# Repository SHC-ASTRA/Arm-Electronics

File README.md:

View this project on [CADLAB.io](https://cadlab.io/project/23351). 

# Arm-Electronics

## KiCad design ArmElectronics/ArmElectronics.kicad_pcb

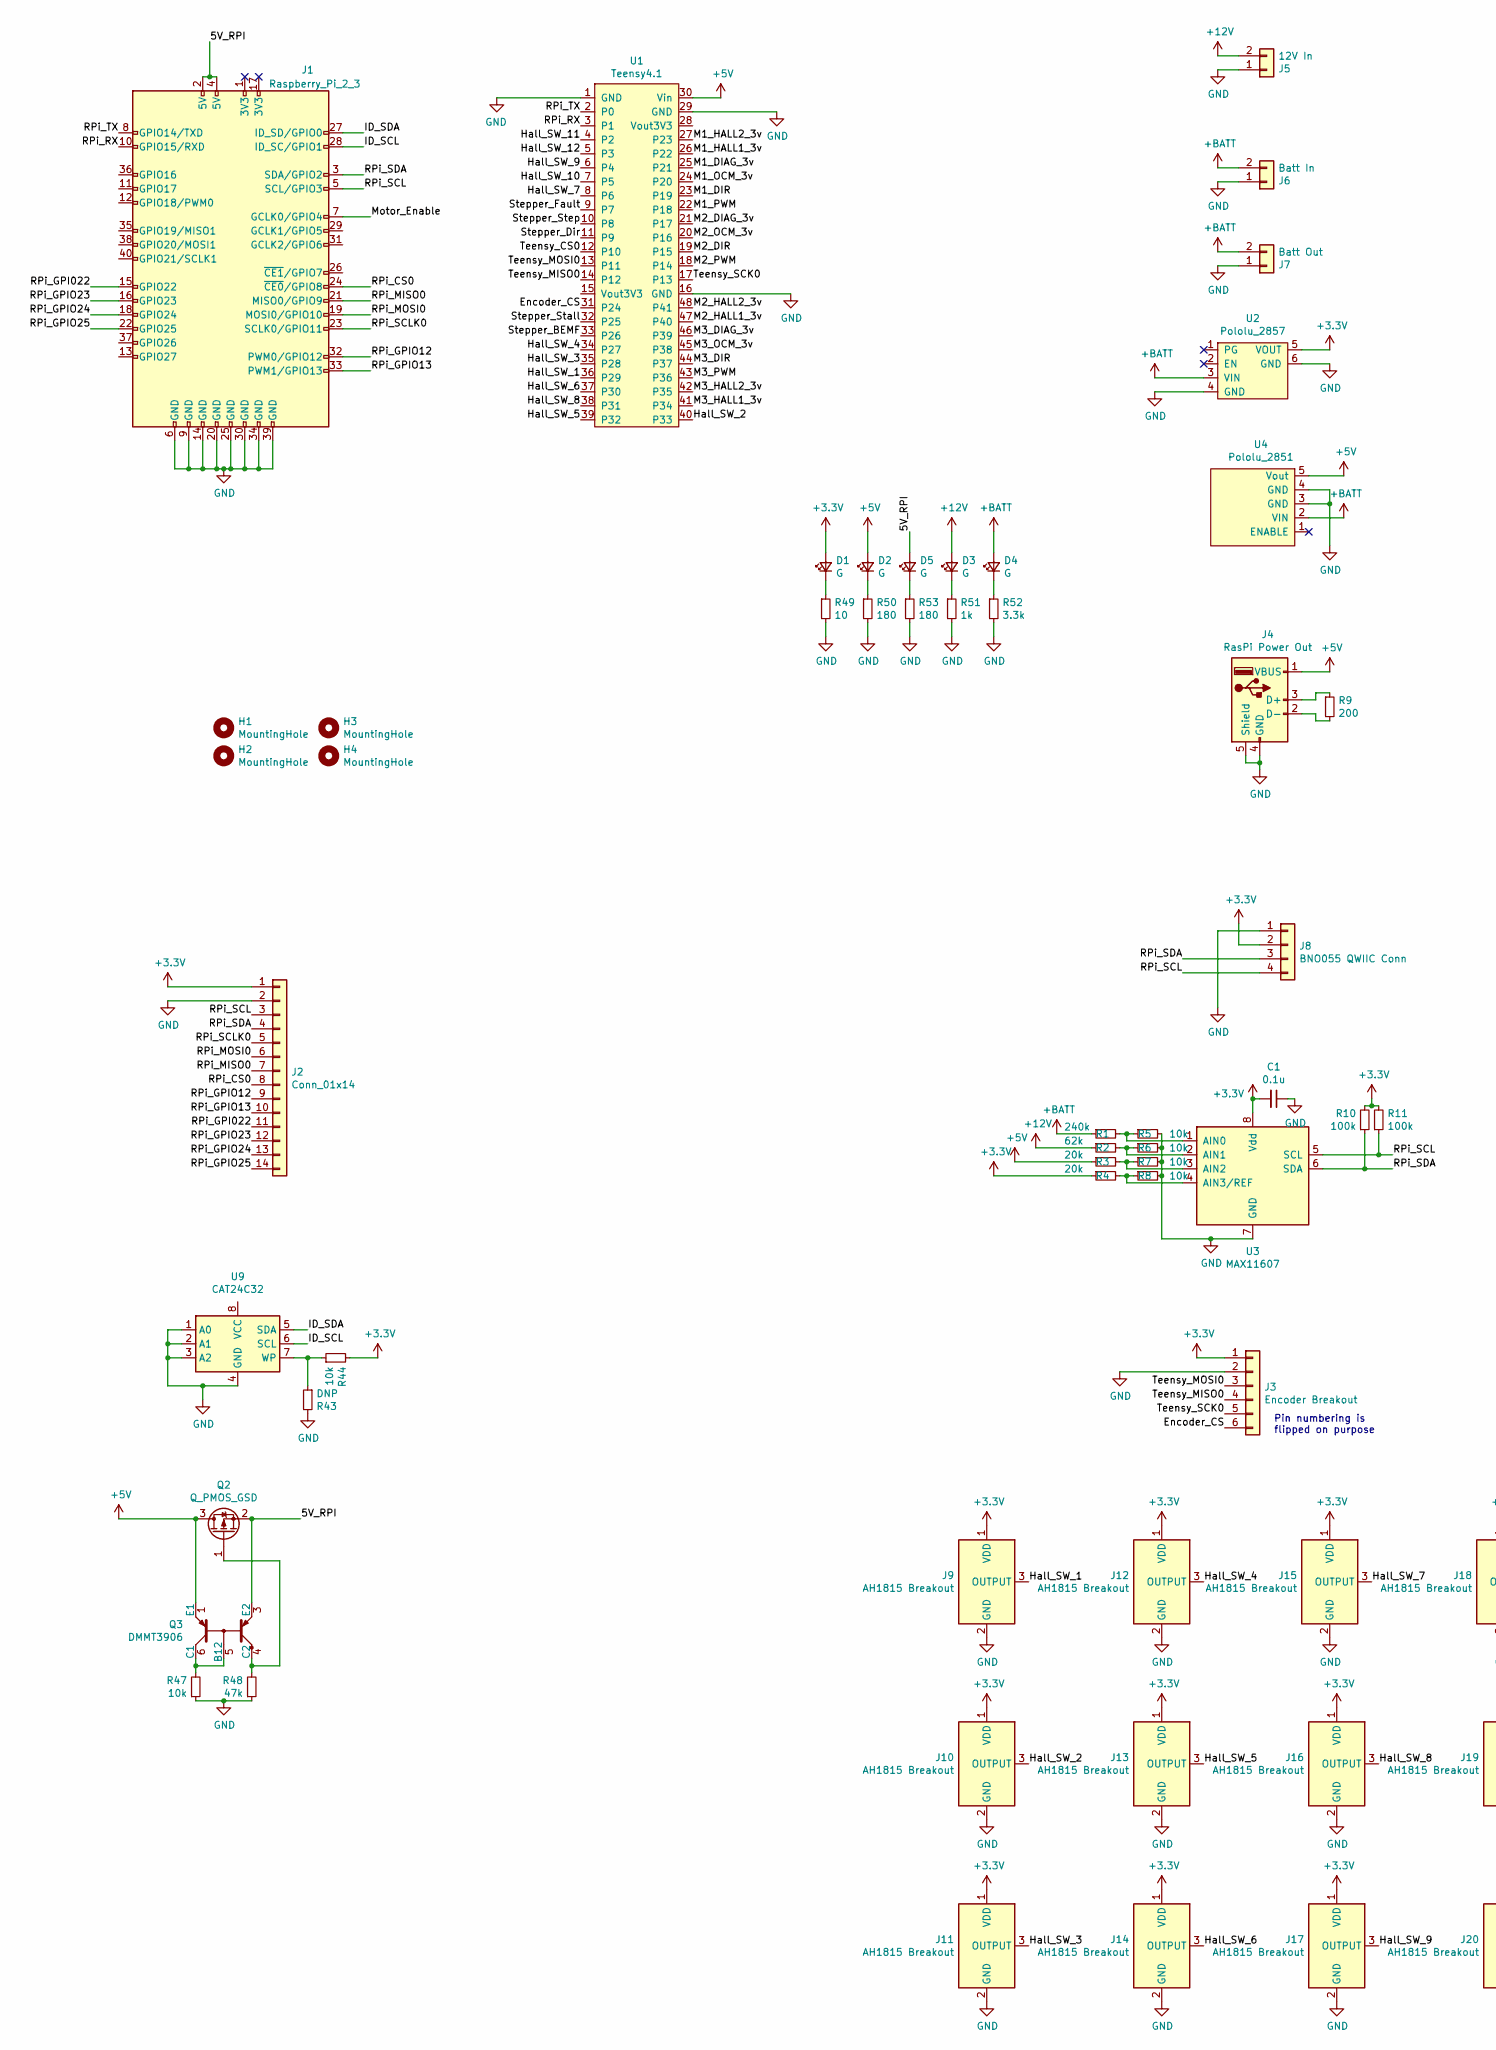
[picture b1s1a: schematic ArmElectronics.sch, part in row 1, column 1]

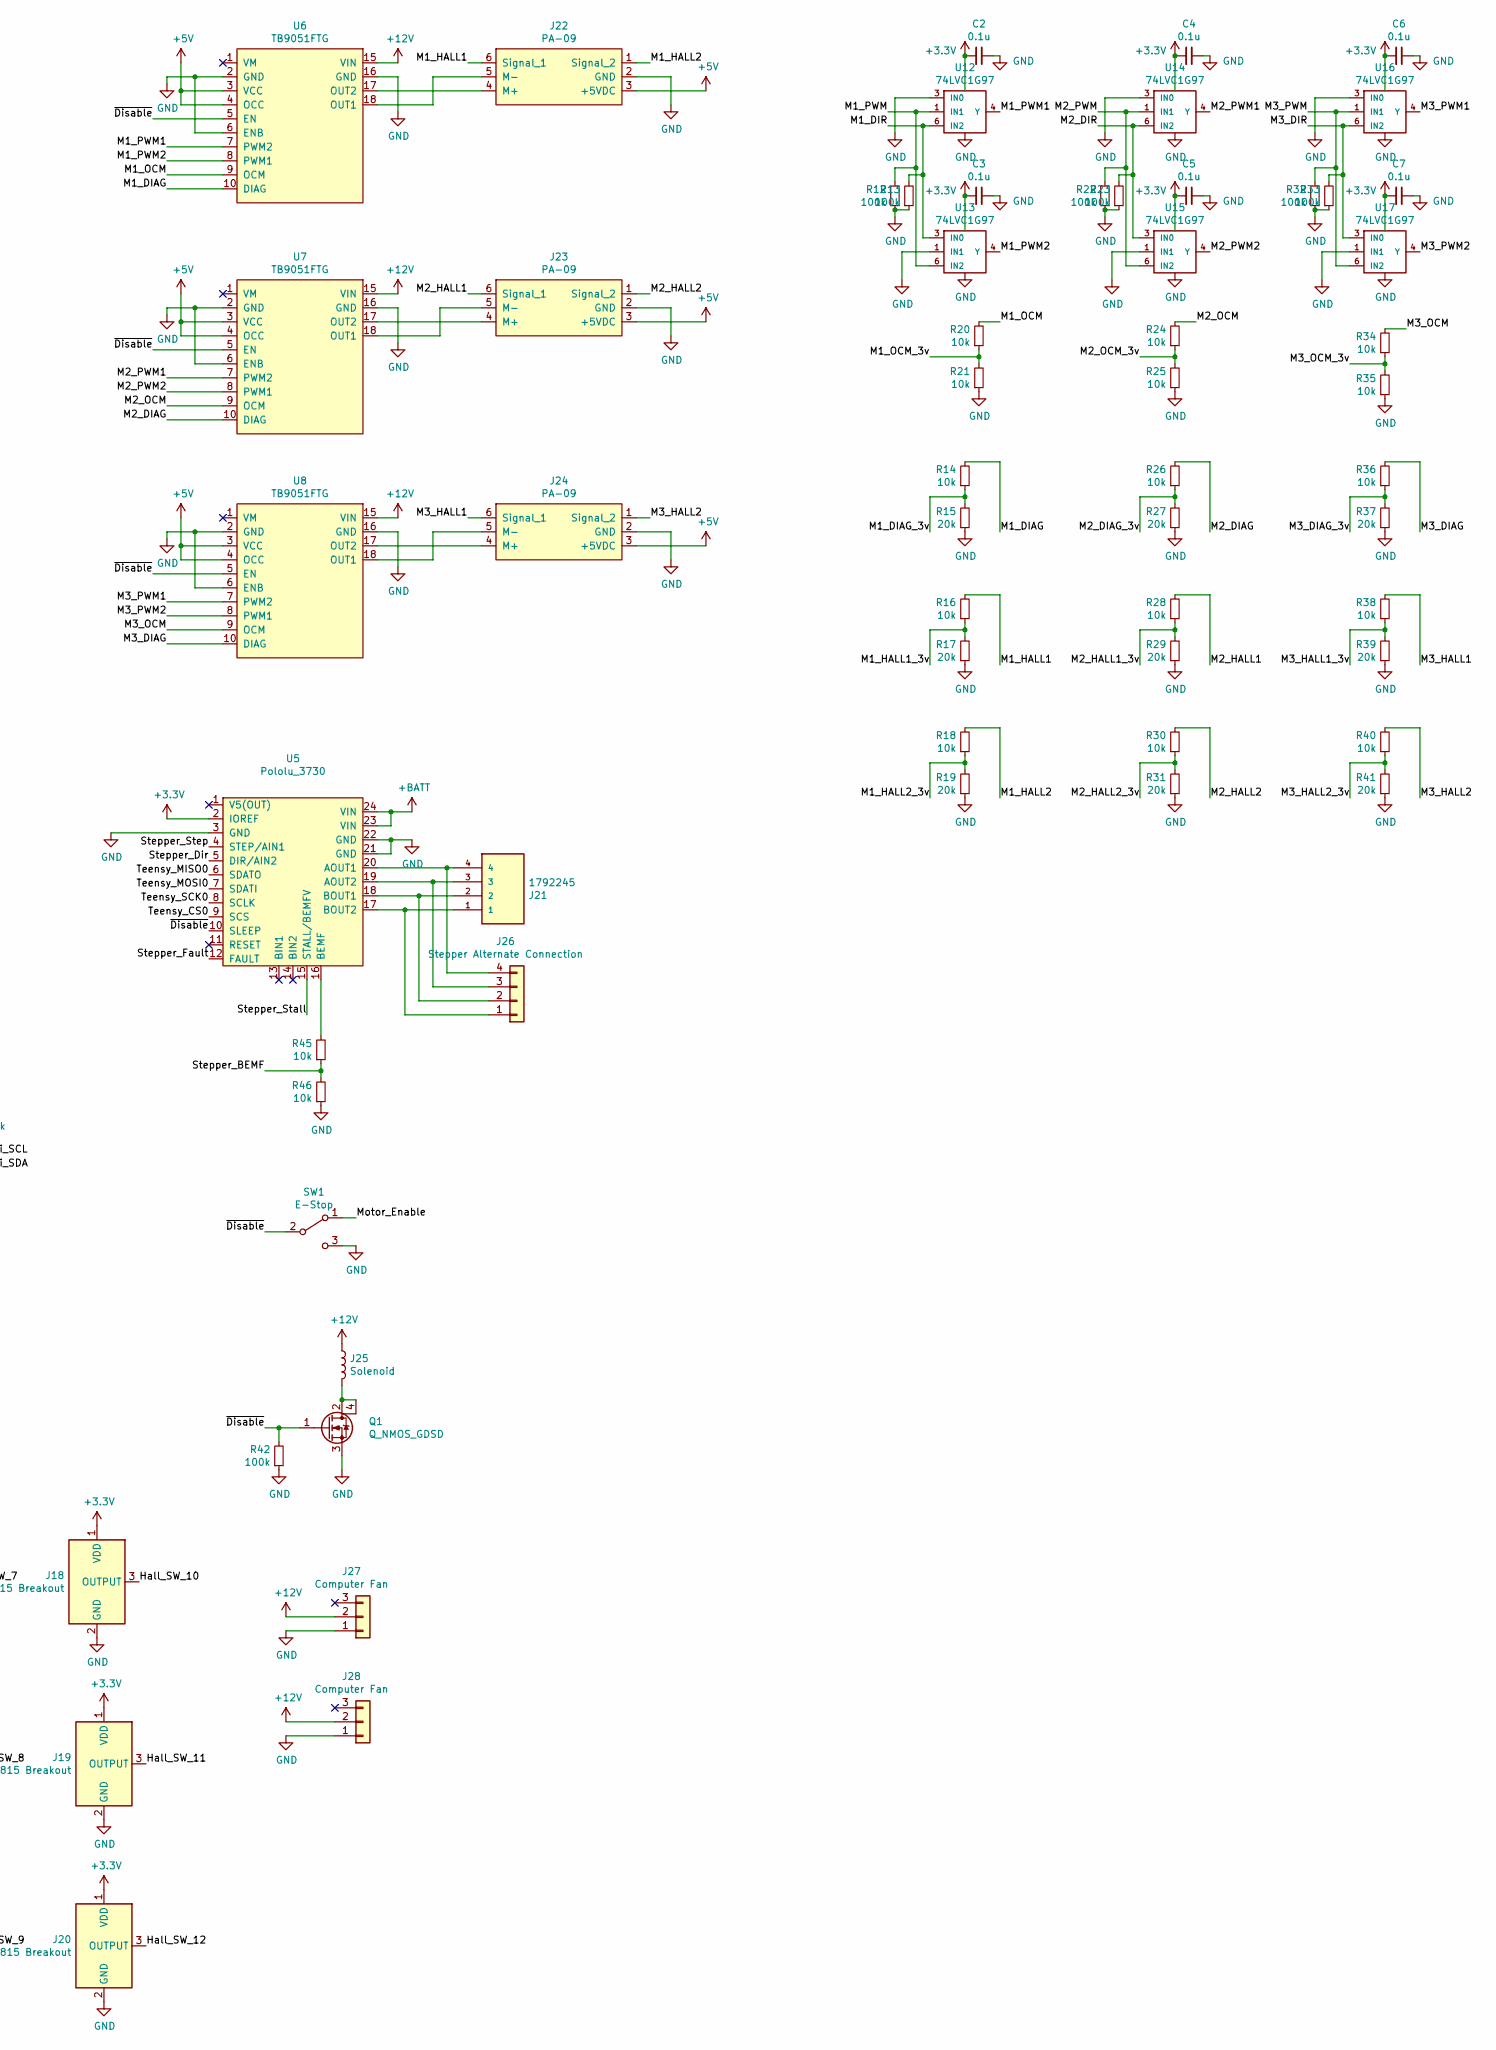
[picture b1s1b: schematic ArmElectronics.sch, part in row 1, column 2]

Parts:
C1, C2, C3, C4, C5, C6, C7: 0.1u; C_0603_1608Metric_Pad1.05x0.95mm_HandSolder; Digikey Part Num 311-1341-1-ND
D1, D2, D3, D4, D5: G; LED_0603_1608Metric_Pad1.05x0.95mm_HandSolder; Digikey Part Num 732-4971-1-ND
H1, H2, H3, H4: MountingHole; MountingHole_3.2mm_M3_Pad
J1: Raspberry_Pi_2_3; IDC-Header_2x20_P2.54mm_Vertical; Digikey Part Num S9175-ND
J2: Conn_01x14; PinSocket_1x14_P2.54mm_Vertical
J3: Encoder Breakout; JST_PH_B6B-PH-K_1x06_P2.00mm_Vertical; Digikey Part Num 455-1708-ND
J4: RasPi Power Out; USB_A_Molex_67643_Horizontal; Digikey Part Num WM14667-ND
J5: 12V In; AMASS_XT60-F_1x02_P7.20mm_Vertical; Digikey Part Num not on Digikey
J6: Batt In; AMASS_XT60-F_1x02_P7.20mm_Vertical; Digikey Part Num not on Digikey
J7: Batt Out; AMASS_XT60-F_1x02_P7.20mm_Vertical; Digikey Part Num not on Digikey
J8: BNO055 QWIIC Conn; JST_SH_SM04B-SRSS-TB_1x04-1MP_P1.00mm_Horizontal; Digikey Part Num 1528-4646-ND
J9, J10, J11, J12, J13, J14, J15, J16, J17, J18, J19, J20: AH1815 Breakout; JST_PH_B3B-PH-K_1x03_P2.00mm_Vertical; Digikey Part Num 455-1705-ND
J21: 1792245; PHOENIX_1792245; PARTREV 29.08.2013; Digikey Part Num 277-9888-ND
J22, J23, J24: PA-09; Molex_Mini-Fit_Jr_5566-06A_2x03_P4.20mm_Vertical; Digikey Part Num WM3802-ND
J25: Solenoid; JST_XH_B2B-XH-A_1x02_P2.50mm_Vertical; Digikey Part Num 455-2247-ND
J26: Stepper Alternate Connection; JST_XH_S4B-XH-A_1x04_P2.50mm_Horizontal; Digikey Part Num 455-2243-ND
J27, J28: Computer Fan; Molex_KK-254_AE-6410-03A_1x03_P2.54mm_Vertical; Digikey Part Num WM2701-ND
Q1: Q_NMOS_GDSD; SOT-223; Digikey Part Num NCV8440ASTT1GOSCT-ND
Q2: Q_PMOS_GSD; SOT-23; Digikey Part Num TSM500P02CXRFGCT-ND
Q3: DMMT3906; SOT-23-6; Digikey Part Num DMMT3906-7-FDICT-ND
R1: 240k; R_0603_1608Metric_Pad0.98x0.95mm_HandSolder; Digikey Part Num P240KGCT-ND
R2: 62k; R_0603_1608Metric_Pad0.98x0.95mm_HandSolder; Digikey Part Num P62KGCT-ND
R3, R4, R15, R17, R19, R27, R29, R31, R37, R39, R41: 20k; R_0603_1608Metric_Pad0.98x0.95mm_HandSolder; Digikey Part Num P20KGCT-ND
R5, R6, R7, R8, R14, R16, R18, R20, R21, R24, R25, R26, R28, R30, R34, R35, R36, R38, R40, R44, R45, R46, R47: 10k; R_0603_1608Metric_Pad0.98x0.95mm_HandSolder; Digikey Part Num P10KGCT-ND
R9: 200; R_0603_1608Metric_Pad0.98x0.95mm_HandSolder; Digikey Part Num P200GCT-ND
R10, R11, R12, R13, R22, R23, R32, R33, R42: 100k; R_0603_1608Metric_Pad0.98x0.95mm_HandSolder; Digikey Part Num P100KGCT-ND
R43: DNP; R_0603_1608Metric_Pad0.98x0.95mm_HandSolder
R48: 47k; R_0603_1608Metric_Pad0.98x0.95mm_HandSolder; Digikey Part Num 311-47.0KHRCT-ND
R49: 10; R_0603_1608Metric; Digikey Part Num 311-10.0HRCT-ND
R50, R53: 180; R_0603_1608Metric; Digikey Part Num 311-180HRCT-ND
R51: 1k; R_0603_1608Metric; Digikey Part Num 311-1.00KHRCT-ND
R52: 3.3k; R_0603_1608Metric; Digikey Part Num 311-3.30KHRCT-ND
SW1: E-Stop; JST_PH_B3B-PH-K_1x03_P2.00mm_Vertical; Digikey Part Num 455-1705-ND
U1: Teensy4.1; Digikey Part Num 1568-DEV-16996-ND
U2: Pololu_2857; Digikey Part Num 2183-2857-ND
U3: MAX11607; TSSOP-8_3x3mm_P0.65mm; Digikey Part Num MAX11607EUA+-ND
U4: Pololu_2851; Digikey Part Num 2183-2851-ND
U5: Pololu_3730; Digikey Part Num 2183-3730-ND
U6, U7, U8: TB9051FTG; Digikey Part Num 2183-2997-ND
U9: CAT24C32; TSSOP-8_4.4x3mm_P0.65mm; Digikey Part Num CAT24C32YI-GT3OSCT-ND
U12, U13, U14, U15, U16, U17: 74LVC1G97; SOT-23-6_Handsoldering; Digikey Part Num 296-15581-1-ND

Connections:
+3V3: C1.2, C2.2, C3.2, C4.2, C5.2, C6.2, C7.2, D1.2 (A), J2.1, J3.1, J8.2, J9.1 (VDD), J10.1 (VDD), J11.1 (VDD), J12.1 (VDD), J13.1 (VDD), J14.1 (VDD), J15.1 (VDD), J16.1 (VDD), J17.1 (VDD), J18.1 (VDD), J19.1 (VDD), J20.1 (VDD), R4.1, R10.2, R11.2, R44.2, U2.5 (VOUT), U3.8 (Vdd), U5.2 (IOREF), U12.5 (VCC), U13.5 (VCC), U14.5 (VCC), U15.5 (VCC), U16.5 (VCC), U17.5 (VCC)
+5V: D2.2 (A), J4.1 (VBUS), J22.3 (+5VDC), J23.3 (+5VDC), J24.3 (+5VDC), Q2.3 (D), Q3.1 (E1), R3.1, U1.30 (Vin), U4.5 (Vout), U6.3 (VCC), U6.4 (OCC), U7.3 (VCC), U7.4 (OCC), U8.3 (VCC), U8.4 (OCC)
+12V: D3.2 (A), J5.2, J25.1, J27.2, J28.2, R2.1, U6.15 (VIN), U7.15 (VIN), U8.15 (VIN)
+BATT: D4.2 (A), J6.2, J7.2, R1.1, U2.3 (VIN), U4.2 (VIN), U5.23 (VIN), U5.24 (VIN)
/5V_RPI: D5.2 (A), J1.2 (5V), J1.4 (5V), Q2.2 (S), Q3.3 (E2)
/Encoder_CS: J3.6, U1.31 (P24)
/Hall_SW_1: J9.3 (OUTPUT), U1.36 (P29)
/Hall_SW_2: J10.3 (OUTPUT), U1.40 (P33)
/Hall_SW_3: J11.3 (OUTPUT), U1.35 (P28)
/Hall_SW_4: J12.3 (OUTPUT), U1.34 (P27)
/Hall_SW_5: J13.3 (OUTPUT), U1.39 (P32)
/Hall_SW_6: J14.3 (OUTPUT), U1.37 (P30)
/Hall_SW_7: J15.3 (OUTPUT), U1.8 (P6)
/Hall_SW_8: J16.3 (OUTPUT), U1.38 (P31)
/Hall_SW_9: J17.3 (OUTPUT), U1.6 (P4)
/Hall_SW_10: J18.3 (OUTPUT), U1.7 (P5)
/Hall_SW_11: J19.3 (OUTPUT), U1.4 (P2)
/Hall_SW_12: J20.3 (OUTPUT), U1.5 (P3)
/ID_SCL: J1.28 (ID_SC/GPIO1), U9.6 (SCL)
/ID_SDA: J1.27 (ID_SD/GPIO0), U9.5 (SDA)
/M1_DIAG: R14.2, U6.10 (DIAG)
/M1_DIAG_3v: R14.1, R15.2, U1.25 (P21)
/M1_DIR: R13.2, U1.23 (P19), U12.6 (IN2), U13.3 (IN0)
/M1_HALL1: J22.6 (Signal_1), R16.2
/M1_HALL1_3v: R16.1, R17.2, U1.26 (P22)
/M1_HALL2: J22.1 (Signal_2), R18.2
/M1_HALL2_3v: R18.1, R19.2, U1.27 (P23)
/M1_OCM: R20.2, U6.9 (OCM)
/M1_OCM_3v: R20.1, R21.2, U1.24 (P20)
/M1_PWM: R12.2, U1.22 (P18), U12.1 (IN1), U13.6 (IN2)
/M1_PWM1: U6.7 (PWM2), U12.4 (Y)
/M1_PWM2: U6.8 (PWM1), U13.4 (Y)
/M2_DIAG: R26.2, U7.10 (DIAG)
/M2_DIAG_3v: R26.1, R27.2, U1.21 (P17)
/M2_DIR: R23.2, U1.19 (P15), U14.6 (IN2), U15.3 (IN0)
/M2_HALL1: J23.6 (Signal_1), R28.2
/M2_HALL1_3v: R28.1, R29.2, U1.47 (P40)
/M2_HALL2: J23.1 (Signal_2), R30.2
/M2_HALL2_3v: R30.1, R31.2, U1.48 (P41)
/M2_OCM: R24.2, U7.9 (OCM)
/M2_OCM_3v: R24.1, R25.2, U1.20 (P16)
/M2_PWM: R22.2, U1.18 (P14), U14.1 (IN1), U15.6 (IN2)
/M2_PWM1: U7.7 (PWM2), U14.4 (Y)
/M2_PWM2: U7.8 (PWM1), U15.4 (Y)
/M3_DIAG: R36.2, U8.10 (DIAG)
/M3_DIAG_3v: R36.1, R37.2, U1.46 (P39)
/M3_DIR: R33.2, U1.44 (P37), U16.6 (IN2), U17.3 (IN0)
/M3_HALL1: J24.6 (Signal_1), R38.2
/M3_HALL1_3v: R38.1, R39.2, U1.41 (P34)
/M3_HALL2: J24.1 (Signal_2), R40.2
/M3_HALL2_3v: R40.1, R41.2, U1.42 (P35)
/M3_OCM: R34.2, U8.9 (OCM)
/M3_OCM_3v: R34.1, R35.2, U1.45 (P38)
/M3_PWM: R32.2, U1.43 (P36), U16.1 (IN1), U17.6 (IN2)
/M3_PWM1: U8.7 (PWM2), U16.4 (Y)
/M3_PWM2: U8.8 (PWM1), U17.4 (Y)
/Motor_Enable: J1.7 (GCLK0/GPIO4), SW1.1 (A)
/RPi_CS0: J1.24 (~CE0~/GPIO8), J2.8
/RPi_GPI022: J1.15 (GPIO22), J2.11
/RPi_GPIO12: J1.32 (PWM0/GPIO12), J2.9
/RPi_GPIO13: J1.33 (PWM1/GPIO13), J2.10
/RPi_GPIO23: J1.16 (GPIO23), J2.12
/RPi_GPIO24: J1.18 (GPIO24), J2.13
/RPi_GPIO25: J1.22 (GPIO25), J2.14
/RPi_MISO0: J1.21 (MISO0/GPIO9), J2.7
/RPi_MOSI0: J1.19 (MOSI0/GPIO10), J2.6
/RPi_RX: J1.10 (GPIO15/RXD), U1.3 (P1)
/RPi_SCL: J1.5 (SCL/GPIO3), J2.3, J8.4, R11.1, U3.5 (SCL)
/RPi_SCLK0: J1.23 (SCLK0/GPIO11), J2.5
/RPi_SDA: J1.3 (SDA/GPIO2), J2.4, J8.3, R10.1, U3.6 (SDA)
/RPi_TX: J1.8 (GPIO14/TXD), U1.2 (P0)
/Stepper_BEMF: R45.1, R46.2, U1.33 (P26)
/Stepper_Dir: U1.11 (P9), U5.5 (DIR/AIN2)
/Stepper_Fault: U1.9 (P7), U5.12 (FAULT)
/Stepper_Stall: U1.32 (P25), U5.15 (STALL/BEMFV)
/Stepper_Step: U1.10 (P8), U5.4 (STEP/AIN1)
/Teensy_CS0: U1.12 (P10), U5.9 (SCS)
/Teensy_MISO0: J3.4, U1.14 (P12), U5.6 (SDATO)
/Teensy_MOSI0: J3.3, U1.13 (P11), U5.7 (SDATI)
/Teensy_SCK0: J3.5, U1.17 (P13), U5.8 (SCLK)
/~Disable: Q1.1 (G), R42.2, SW1.2 (B), U5.10 (SLEEP), U6.5 (EN), U7.5 (EN), U8.5 (EN)
GND: C1.1, C2.1, C3.1, C4.1, C5.1, C6.1, C7.1, J1.6 (GND), J1.9 (GND), J1.14 (GND), J1.20 (GND), J1.25 (GND), J1.30 (GND), J1.34 (GND), J1.39 (GND), J2.2, J3.2, J4.4 (GND), J4.5 (Shield), J5.1, J6.1, J7.1, J8.1, J9.2 (GND), J10.2 (GND), J11.2 (GND), J12.2 (GND), J13.2 (GND), J14.2 (GND), J15.2 (GND), J16.2 (GND), J17.2 (GND), J18.2 (GND), J19.2 (GND), J20.2 (GND), J22.2 (GND), J23.2 (GND), J24.2 (GND), J27.1, J28.1, Q1.3 (S), R5.2, R6.2, R7.2, R8.2, R12.1, R13.1, R15.1, R17.1, R19.1, R21.1, R22.1, R23.1, R25.1, R27.1, R29.1, R31.1, R32.1, R33.1, R35.1, R37.1, R39.1, R41.1, R42.1, R43.2, R46.1, R47.1, R48.1, R49.2, R50.2, R51.2, R52.2, R53.2, SW1.3 (C), U1.1 (GND), U1.16 (GND), U1.29 (GND), U2.4 (GND), U2.6 (GND), U3.7 (GND), U4.3 (GND), U4.4 (GND), U5.3 (GND), U5.21 (GND), U5.22 (GND), U6.2 (GND), U6.6 (ENB), U6.16 (GND), U7.2 (GND), U7.6 (ENB), U7.16 (GND), U8.2 (GND), U8.6 (ENB), U8.16 (GND), U9.1 (A0), U9.2 (A1), U9.3 (A2), U9.4 (GND), U12.2 (GND), U12.3 (IN0), U13.1 (IN1), U13.2 (GND), U14.2 (GND), U14.3 (IN0), U15.1 (IN1), U15.2 (GND), U16.2 (GND), U16.3 (IN0), U17.1 (IN1), U17.2 (GND)
unnamed: D1.1 (K), R49.1
unnamed: D2.1 (K), R50.1
unnamed: D3.1 (K), R51.1
unnamed: D4.1 (K), R52.1
unnamed: D5.1 (K), R53.1
unnamed: J4.2 (D-), R9.2
unnamed: J4.3 (D+), R9.1
unnamed: J21.1, J26.1, U5.17 (BOUT2)
unnamed: J21.2, J26.2, U5.18 (BOUT1)
unnamed: J21.3, J26.3, U5.19 (AOUT2)
unnamed: J21.4, J26.4, U5.20 (AOUT1)
unnamed: J22.4 (M+), U6.17 (OUT2)
unnamed: J22.5 (M-), U6.18 (OUT1)
unnamed: J23.4 (M+), U7.17 (OUT2)
unnamed: J23.5 (M-), U7.18 (OUT1)
unnamed: J24.4 (M+), U8.17 (OUT2)
unnamed: J24.5 (M-), U8.18 (OUT1)
unnamed: J25.2, Q1.2 (D), Q1.4 (D)
unnamed: Q2.1 (G), Q3.4 (C2), R48.2
unnamed: Q3.5 (B12), Q3.6 (C1), R47.2
unnamed: R1.2, R5.1, U3.1 (AIN0)
unnamed: R2.2, R6.1, U3.2 (AIN1)
unnamed: R3.2, R7.1, U3.3 (AIN2)
unnamed: R4.2, R8.1, U3.4 (AIN3/REF)
unnamed: R43.1, R44.1, U9.7 (WP)
unnamed: R45.2, U5.16 (BEMF)

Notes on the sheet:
Pin numbering is flipped on purpose

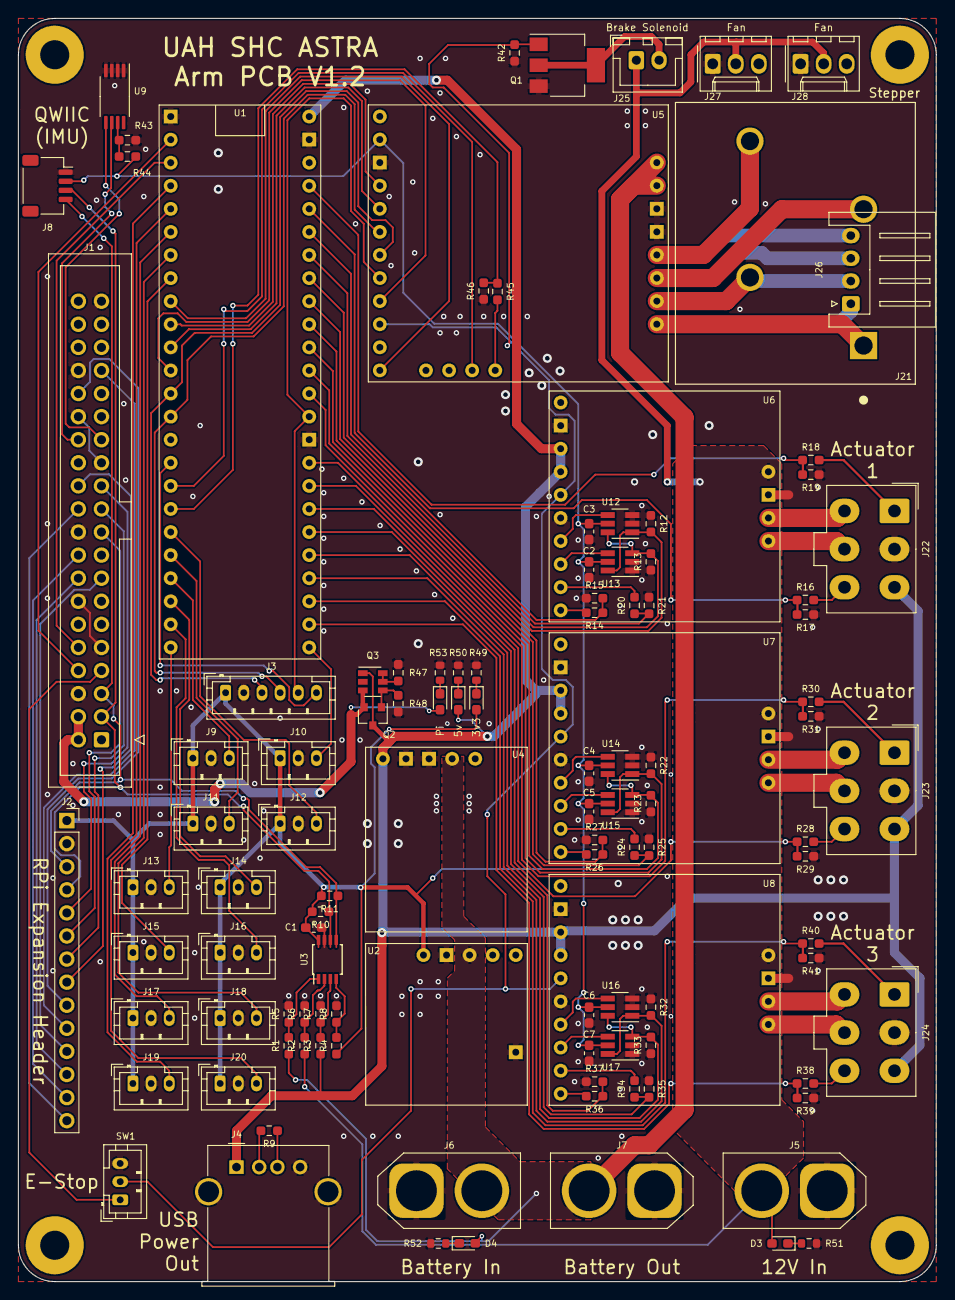
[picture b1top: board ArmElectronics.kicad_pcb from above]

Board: 2 copper layers, 101.0 x 139.0 mm, 116 parts (0 on the bottom side), 108 nets.

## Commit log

2020-09-22 Backlink to CADLAB.io has been added.
2020-09-22 Added files
2020-09-28 Added major components with already existing symbols
2020-09-29 Added a mini library with the Pololu 2851
2020-09-29 Added in Pololu2581
2020-09-29 SFPololu2857
    Added Pololu 2857 to library.
2020-09-29 Created the teensy 4.1 schematic symbol
2020-09-29 Fixed pins outside of rectangle
2020-09-29 Fixed a weird error
2020-10-10 Added actuator symbols
2020-10-10 Copy Aiden Library into main
2020-10-10 Added motor controller to library
2020-10-12 Finished motor drivers and motors
    (Not connected to teensy)
2020-10-12 Little cleanup
2020-10-12 Power section
2020-10-13 forgot that connecting different logic voltages together lets the magic smoke out
2020-10-13 Small changes
2020-10-19 connected rpi and teensy
2020-11-03 Started footprints
2020-11-15 Added 3 footprints
    Added footprints for Pololu_2581, _2587, and TB9.
2020-11-16 Added teensy 4.1 footprint
    Added 1 footprint
2020-11-16 Fixed typo in 2851
2020-11-16 changed power architecture, moved bno to connector, associated footprints
2020-11-16 added M3 mounting holes
2020-11-16 Added pololu 3730 and minor footprint changes
    Added 3730 symbol and footprint. Minor edits to teensy 4.1 footprint
2020-11-16 added part nums
2020-11-16 Added some 3D models I found, started stepper driver
2020-11-16 I think the schematic is done?
2020-11-16 Setup PCB
2020-11-17 Loaded netlist into PCB file
2020-11-17 Added additional part num
2020-11-17 Start of Thomas' PCB attempt
2020-11-17 Schematic thing
    Will be rendered obsolete with changes to transistors and such
2020-11-17 Actually though about logic level shifting properly
2020-11-17 fixed j9
2020-11-17 re-updated PCB
2020-11-17 Forgot some supporting components for logic gates
2020-11-18 Routed drivers and motors, fixed errors on schematic
2020-11-20 PCB work continues
2020-11-20 PCB theoretically complete (Also I just realized I've been making these changes in master not my branch oof)
2020-11-20 not quite sure what I changed but github says something's different so IDK
2020-11-20 I think it worked?
2020-11-20 Tweaks
2020-11-20 Added text
2020-11-22 Added some new sensors to schematic, designed breakout board
2020-11-22 Hall switches added
2020-11-22 Symbol and footprint cleanup for drivers
2020-11-22 Updated PCB for new schematic
2020-11-22 reannotated schematic
2020-11-22 forgot to hit save in eeschema
2020-11-22 Please be done now
2020-11-22 It wasn't done :frowning:
2020-11-22 Added an E-Stop switch and motor off function
2020-11-22 Added brake solenoid for axis 0
2020-11-22 Added some 3d models
2020-11-22 Forgot to fill a zone
2020-11-23 added an alternate stepper connector
2020-12-02 Added fan connectors
2020-12-04 Added fans
2022-03-14 post SAR updates
2022-03-14 Implemented post SAR fixes
2022-03-15 NOT DONE FIX U3 AND SILKSCREEN
2022-03-17 Indicator LEDs
2022-03-17 Ready to order?
2022-03-19 Changed a component
